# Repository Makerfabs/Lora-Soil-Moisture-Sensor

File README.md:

# Lora Soil Moisture Sensor

[toc]

# Makerfabs

[Makerfabs home page](https://www.makerfabs.com/)

[Makerfabs Wiki](https://makerfabs.com/wiki/index.php?title=Main_Page)

# Lora Soil Moisture Sensor

## Introduce

Product Link: [Lora_Soil_Moisture_Sensor](https://www.makerfabs.com/lora-soil-moisture-sensor.html)

Wiki Link:  [Lora_Soil_Moisture_Sensor_V3](https://www.makerfabs.com/wiki/index.php?title=Lora_Soil_Moisture_Sensor_V3)

The Lora soil moisture sensor is based on Atmel's Atmega328P, it collects local air temperature/ humidity with sensor AHT10, and detect the soil humidity with capacitor-humility measurement solution with MCU clock, and transmit the local environment data to the gateway, with Lora communication, suit for applications for smart-farm, irrigation, agriculture, etc. 

In applications, always you do not need to check the air/soil state continuously, have a test of them for few seconds after then minutes/hours sleeping is normally Ok for most projects. To save power, there the Air/ Soil measuring functional could be shut down in the working, so they can be only powered ON a short time and then a long time power off. With MCU in sleeping mode and low power consumption Lora module, this module works ok with 2 AAA battery more than one year. Besides, this sensor is coated with waterproof paint, which makes it longer working time in damp soil. 

## Feature

- Classic ATMEL AVR 8-bit Atmega328P, with Arduino Pro Mini(3.3V/8M bootloader pre-loaded) .
- Capacitor-humility measurement.
- AHT10 temperature and humidity sensor.
- Working with 2 AAA more than one years.
- 3D printed case.
- Waterproof coating.
- Unique ID, can be used directly without secondary programming.

# Version
## V3 
In the latest version, the 555 chip has been removed so that the sleep current can be as low as 7.1uA. And added UID, can be used directly.

**More details, see readme. md in the [V3](https://github.com/Makerfabs/Lora-Soil-Moisture-Sensor/tree/master/V3) folder.**
# Makerfabs Soil Moisture Sensor V3 For the Helium Network
Adapted from <https://hackaday.io/project/180796-lorawan-soil-moisture-sensor>

## Equipment needed:

|Sensor|<https://www.makerfabs.com/lora-soil-moisture-sensor-v3.html>||
| :- | :- | :- |
|3.3V USB to TTL / Serial converter|<https://www.makerfabs.com/cp2104-usb-to-serial-converter.html>|Makerfabs recommended|
||<https://ftdichip.com/products/ttl-232r-3v3/>|Arduino recommended|
||<https://www.sparkfun.com/products/9873>|Arduino recommended|
||[https://www.amazon.com/Serial-Adapter-Signal-Prolific-Windows/dp/B07R8BQYW1/](https://www.amazon.com/Serial-Adapter-Signal-Prolific-Windows/dp/B07R8BQYW1/ref=rvi_sccl_3/130-8941171-3218759?pd_rd_w=pLTyv&content-id=amzn1.sym.f5690a4d-f2bb-45d9-9d1b-736fee412437&pf_rd_p=f5690a4d-f2bb-45d9-9d1b-736fee412437&pf_rd_r=2VXNT4N0YP2KE4HXH7XZ&pd_rd_wg=rzSKu&pd_rd_r=5e7c75ef-e88f-4056-a7fc-fb7d07ab074c&pd_rd_i=B07R8BQYW1&psc=1)|Not ideal, but what I had lying around|
||[https://www.amazon.com/dp/B07X4ZTRD2](https://www.amazon.com/dp/B07X4ZTRD2?psc=1&ref=ppx_yo2ov_dt_b_product_details)|did NOT work|
|Dupont wire and header pins||optional depending on converter|

## Connecting and uploading to the board:

1. Use EITHER the power output of the USB-TTL converter OR batteries to power the sensor, not both
2. If the USB-TTL converter does not have DTR, you must use the RST button on the sensor to upload a sketch: hold down RST, press upload, wait until the status shows "uploading", immediately release RST
3. If connection does not work, try reversing RX and TX
4. What worked for me: sensor powered by batteries; converter GND, RX, TX only connected, RX-TX reversed

## Software needed:
* MCCI LoRaWAN LMIC library <https://github.com/mcci-catena/arduino-lmic>
* Lightweight low power library for Arduino <https://github.com/rocketscream/Low-Power>
* For original source code and additional information, refer to: <https://hackaday.io/project/180796-lorawan-soil-moisture-sensor>

## Helium setup:
1. Pay careful attention to the byte order and order of the variables APPEUI, DEVEUI, APPKEY. These are different than what is displayed in the helium console by default
2. The decoder here is provided for reference, it has not been modified to work on the helium console

## Reference info:

* ATMEL AVR 8-bit Atmega328P, with Arduino Pro Mini(3.3V/8M bootloader pre-loaded)
* AHT10 temperature and humidity sensor
* <https://docs.arduino.cc/retired/getting-started-guides/ArduinoProMini>

## V2
Old version, containing 555 chip. A number of items are provided as references.

**More details, see readme. md in the [V2](https://github.com/Makerfabs/Lora-Soil-Moisture-Sensor/tree/master/V2) folder.**

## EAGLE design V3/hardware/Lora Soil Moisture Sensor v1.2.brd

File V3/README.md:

# Lora Soil Moisture Sensor V3

```c++
/*
Version:		V5.0
Author:			UNKOWN
Create Date:	UNKOWN
Note:
	2021/12/15	V5.2: Fix RadioHead demo can't setModemConfig. 
	2021/11/17  V5.1: Fix code bug,example "ESP32 Receiver" pin define wrong.
	2021/10/22	V5.0: Modify the document structure. 
	2021/9/26	V4.0: The new hardware removed the 555 chip, updated the BOM, and significantly improved battery life.
	2021/8/24	V3.1: Now can read ADC value without 555.
	2021/7/22	V3.0: Now support Lorawan to TTN.
	2020/10/26	v2.2: Add a power-save verson.Using watch dog and sleep mode.
	2020/8/24	v2.1: Add pcb file.
    2020/7/24	v2.0: Rebuid readme,add pic. By Vincent
*/
```

[toc]

# Makerfabs

[Makerfabs home page](https://www.makerfabs.com/)

[Makerfabs Wiki](https://makerfabs.com/wiki/index.php?title=Main_Page)

# Lora Soil Moisture Sensor V3

## Introduce

Product Link: [Lora_Soil_Moisture_Sensor](https://www.makerfabs.com/lora-soil-moisture-sensor.html)

Wiki Link:  [Lora_Soil_Moisture_Sensor_V3](https://www.makerfabs.com/wiki/index.php?title=Lora_Soil_Moisture_Sensor_V3)

The Lora soil moisture sensor is based on Atmel's Atmega328P, it collects local air temperature/ humidity with sensor AHT10, and detect the soil humidity with capacitor-humility measurement solution with MCU clock, and transmit the local environment data to the gateway, with Lora communication, suit for applications for smart-farm, irrigation, agriculture, etc. 

In applications, always you do not need to check the air/soil state continuously, have a test of them for few seconds after then minutes/hours sleeping is normally Ok for most projects. To save power, there the Air/ Soil measuring functional could be shut down in the working, so they can be only powered ON a short time and then a long time power off. With MCU in sleeping mode and low power consumption Lora module, this module works ok with 2 AAA battery more than one year. Besides, this sensor is coated with waterproof paint, which makes it longer working time in damp soil. 

## Feature

- Classic ATMEL AVR 8-bit Atmega328P, with Arduino Pro Mini(3.3V/8M bootloader pre-loaded) .
- Capacitor-humility measurement.
- AHT10 temperature and humidity sensor.
- Working with 2 AAA more than one years.
- 3D printed case.
- Waterproof coating.
- Unique ID, can be used directly without secondary programming.

## Hardware Update

We removed the 555 chip and made a lot of changes to the code. The current soil moisture test uses MCU clock pulses instead of those generated by the 555 chip. Sleep mode has also been optimized more.

Detailed power consumption data is being edited....

## Firmware

### Moisture_LowPower_RadioLib_v2.1.ino

The latest firmware is in:

V3\firmware\Moisture_LowPower_RadioLib_v2.1

### How to use
- The code contains a unique ID and sends Lora messages every 75 minutes in the following format:

```c++
String message = 
    "INEDX:" + (String)packetnum + " H:" + (String)humidity + 
    " T:" + (String)temperature + " ADC:" + (String)sensorValue + 
    " BAT:" + (String)batValue;

String back_str = node_id + " REPLY : SOIL " + message;

//Full message example:
//ID010123 REPLY : SOIL INEDX:0 H:48.85 T:30.50 ADC:896 BAT:1016
```

- If you want to change the time, you can change it:

```c++
//Set sleep time, when value is 1 almost sleep 20s,when value is 450, almost 1 hour.
//Each sleep cycle almost 8s.
#define SLEEP_CYCLE 1

```

- The degree of soil ADC is about 900 in air (completely dry) and 600 in water (completely wet).

## Usage

### Receiver

A simple receiver demo is provided. You can use another Lora Moisture or Maduino Lora Radio as the receiver.

Receive data through serial port display.

The receiver code is in: V3\example\Lora_Receiver_v1.0

### ESP32 Receiver

A simple receiver demo is provided. You can use a MakePython Lora as the receiver.

Receive data and display on SSD1306.

### RadioHead Demo

The default parameters of RadioLib can reach about 800m communication distance, of course can be further, but we do not have time to debug Lora parameters.

We provide an example that can reach 1.7km communication distance, which was debugged by a former colleague. It used to depend on some AVR libraries This made ESP32 unable to complier ReadHead library at the time, so we switched to RadioLib instead. But the latest version, ReadHead is available under ESP32.

Please download the latest [RadioHead](http://www.airspayce.com/mikem/arduino/RadioHead/)

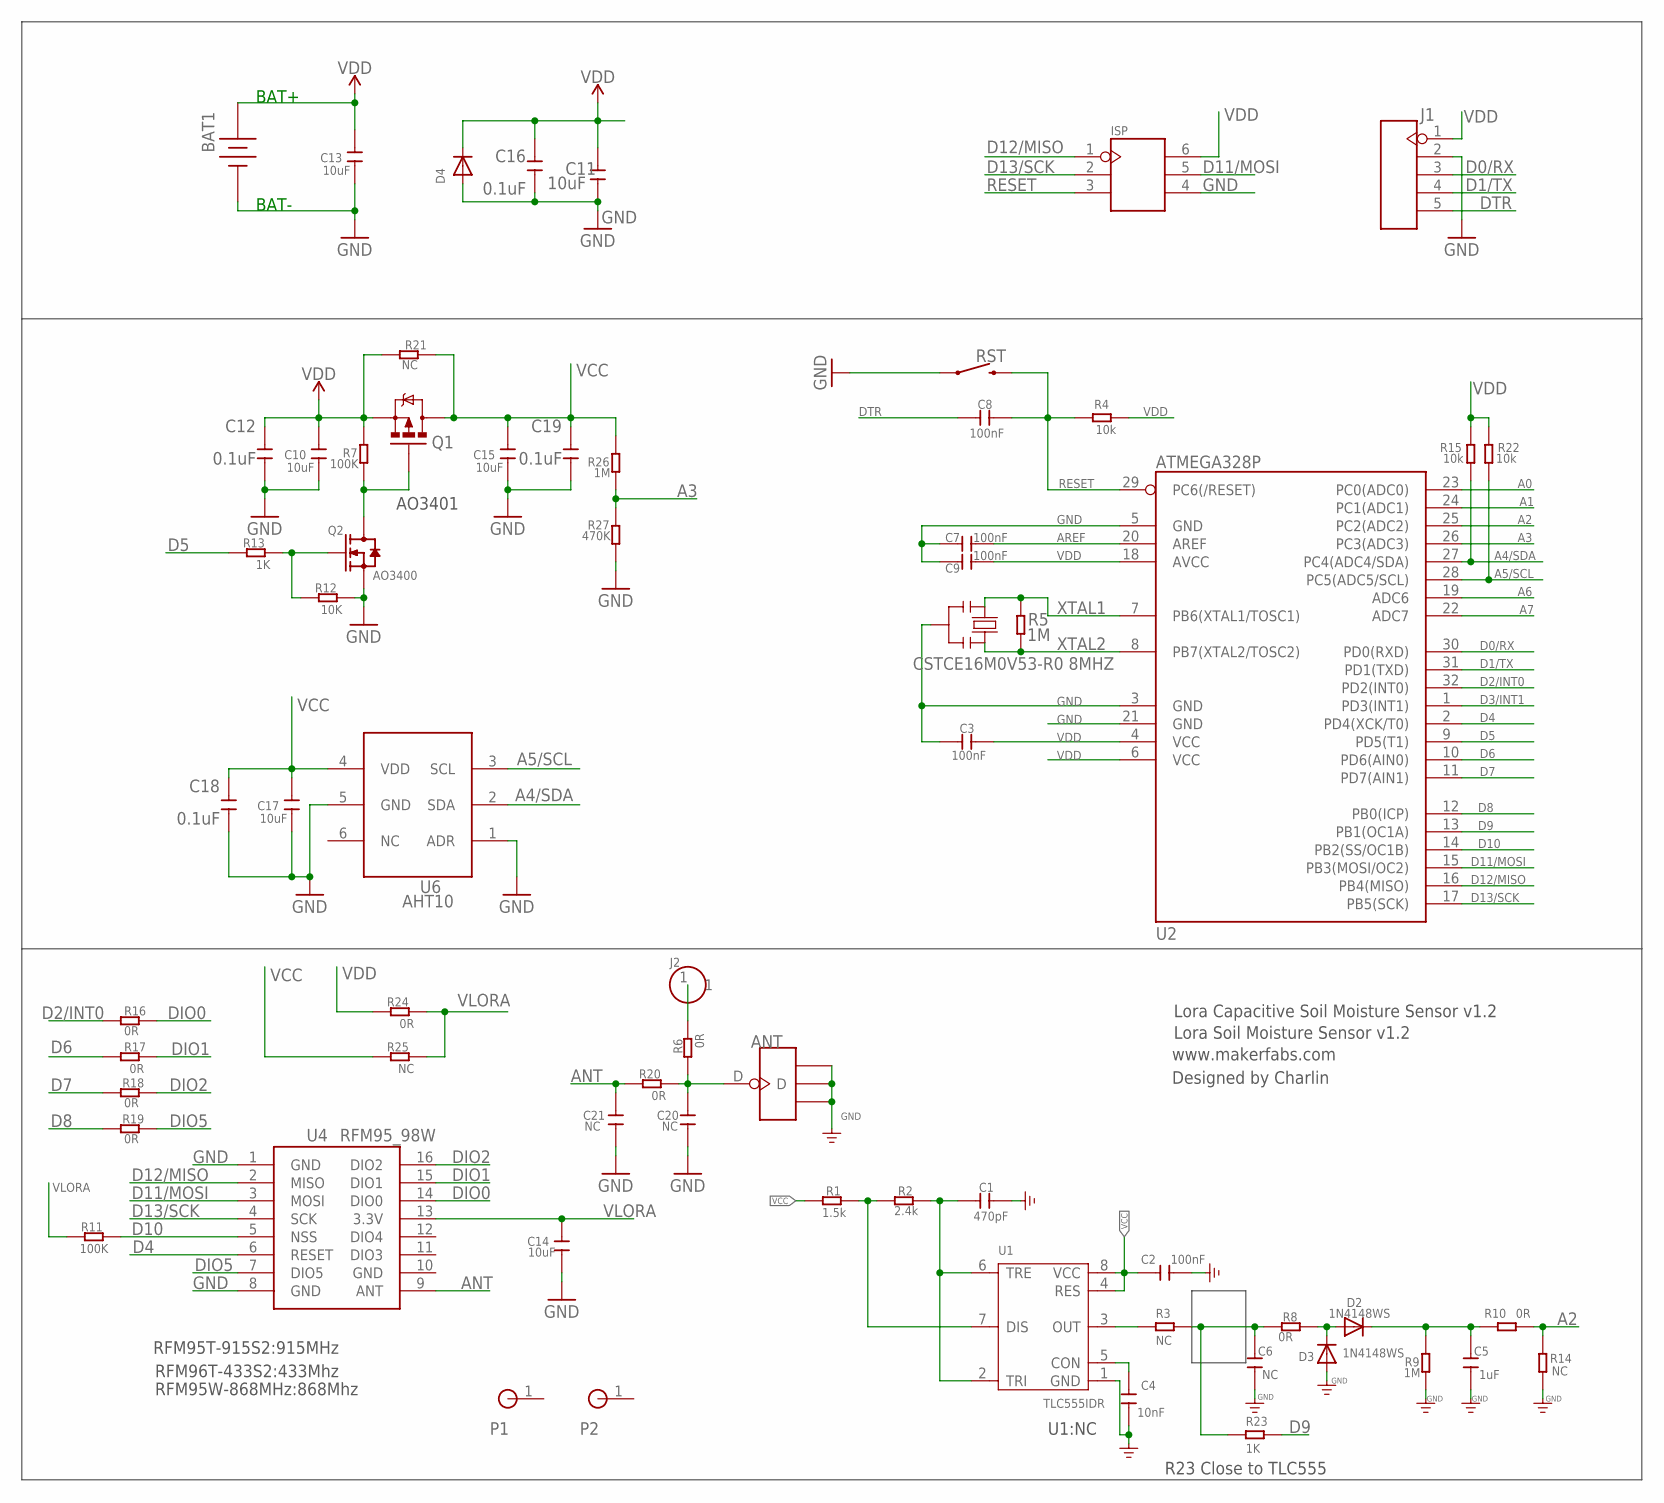
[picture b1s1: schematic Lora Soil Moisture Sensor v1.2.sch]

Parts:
ANT: ANTENNA-U-FL; 4P-U-FL
BAT1: 18650
C1: 470pF; C0603
C2: 100nF; C0603
C3, C7, C8, C9: 100nF; 0603
C4: 10nF; C0603
C5: 1uF; DISCRETE_C0603
C6: NC; DISCRETE_C0603
C10, C11, C13, C14, C15, C17: 10uF; 0603
C12, C16, C18, C19: 0.1uF; 0603
C20, C21: NC; 0603
D2, D3: 1N4148WS; SOD-323F
D4: DIODESOD-323F; SOD-323F
ISP: HEADER-2X3P-SMD; 2X3P-2.54-SMD
J1: HEADER-5P-2.54; 5P-2.54
J2: HEADER-1P-50; 1P-100/50MIL
P1, P2: HOLE-P1-2.2; MTGNP1-220-1MM
Q1: MOSFET-PCHANNEL; SOT23-3
Q2: AO3400; DISCRETE_SOT23
R1: 1.5k; R0603
R2: 2.4k; R0603
R3, R14, R21, R25: NC; R0603
R4, R15, R22: 10k; R0603
R5, R9, R26: 1M; R0603
R6, R8, R10, R16, R17, R18, R19, R20, R24: 0R; R0603
R7, R11: 100K; R0603
R12: 10K; R0603
R13, R23: 1K; R0603
R27: 470K; R0603
RST: MOMENTARY-SWITCH-SPST-SMD-6.0X3.5MM; TACTILE_SWITCH_SMD_6.0X3.5MM
U1: TLC555IDR; SOIC8-1.27-5X4MM
U2: ATMEGA328P; TQFP32
U4: RFM95_98W; RFM92_93W
U6: AHT10; SMD6-127P-400L500W
Y1: CSTCE16M0V53-R0 8MHZ; RESONATOR

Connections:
A0: U2.23 (PC0(ADC0))
A1: U2.24 (PC1(ADC1))
A2: R10.2, R14.1, U2.25 (PC2(ADC2))
A3: R26.1, R27.2, U2.26 (PC3(ADC3))
A4/SDA: R15.2, U2.27 (PC4(ADC4/SDA)), U6.2 (SDA)
A5/SCL: R22.2, U2.28 (PC5(ADC5/SCL)), U6.3 (SCL)
A6: U2.19 (ADC6)
A7: U2.22 (ADC7)
ANT: C21.2, R20.2, U4.9 (ANT)
AREF: C7.2, U2.20 (AREF)
D0/RX: J1.3, U2.30 (PD0(RXD))
D1/TX: J1.4, U2.31 (PD1(TXD))
D2/INT0: R16.1, U2.32 (PD2(INT0))
D3/INT1: U2.1 (PD3(INT1))
D4: U2.2 (PD4(XCK/T0)), U4.6 (RESET)
D5: R13.2, U2.9 (PD5(T1))
D6: R17.1, U2.10 (PD6(AIN0))
D7: R18.1, U2.11 (PD7(AIN1))
D8: R19.1, U2.12 (PB0(ICP))
D9: R23.2, U2.13 (PB1(OC1A))
D10: R11.1, U2.14 (PB2(SS/OC1B)), U4.5 (NSS)
D11/MOSI: ISP.5, U2.15 (PB3(MOSI/OC2)), U4.3 (MOSI)
D12/MISO: ISP.1, U2.16 (PB4(MISO)), U4.2 (MISO)
D13/SCK: ISP.2, U2.17 (PB5(SCK)), U4.4 (SCK)
DIO0: R16.2, U4.14 (DIO0)
DIO1: R17.2, U4.15 (DIO1)
DIO2: R18.2, U4.16 (DIO2)
DIO5: R19.2, U4.7 (DIO5)
DTR: C8.1, J1.5
GND: ANT.GND1, ANT.GND2, ANT.GND3, BAT1.2, C1.1, C2.1, C3.1, C4.2, C5.1, C6.1, C7.1, C9.1, C10.1, C11.1, C12.1, C13.1, C14.1, C15.1, C16.1, C17.1, C18.1, C19.1, C20.1, C21.1, D3.A, D4.A, ISP.4, J1.2, Q2.2 (S), R9.1, R12.1, R14.2, R27.1, RST.1, U1.1 (GND), U2.3 (GND), U2.5 (GND), U2.21 (GND), U4.1 (GND), U4.8 (GND), U4.10 (GND), U6.1 (ADR), U6.5 (GND), Y1.2
unnamed: R1.1, R2.2, U1.7 (DIS)
unnamed: C1.2, R2.1, U1.2 (TRI), U1.6 (TRE)
unnamed: C4.1, U1.5 (CON)
unnamed: R3.1, U1.3 (OUT)
unnamed: C6.2, R3.2, R8.1, R23.1
unnamed: J2.1, R6.1
unnamed: Q1.1 (G), Q2.3 (D), R7.1
unnamed: D2.A, D3.C, R8.2
unnamed: Q2.1 (G), R12.2, R13.1
unnamed: C5.2, D2.C, R9.2, R10.1
unnamed: ANT.D, C20.2, R6.2, R20.1
RESET: C8.2, ISP.3, R4.2, RST.2, U2.29 (PC6(/RESET))
VCC: C2.2, C15.2, C17.2, C18.2, C19.2, Q1.3 (D), R1.2, R21.1, R25.2, R26.2, U1.4 (RES), U1.8 (VCC), U6.4 (VDD)
VDD: BAT1.1, C3.2, C9.2, C10.2, C11.2, C12.2, C13.2, C16.2, D4.C, ISP.6, J1.1, Q1.2 (S), R4.1, R7.2, R15.1, R21.2, R22.1, R24.2, U2.4 (VCC), U2.6 (VCC), U2.18 (AVCC)
VLORA: C14.2, R11.2, R24.1, R25.1, U4.13 (3.3V)
XTAL1: R5.2, U2.7 (PB6(XTAL1/TOSC1)), Y1.1
XTAL2: R5.1, U2.8 (PB7(XTAL2/TOSC2)), Y1.3

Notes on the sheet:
RFM95T-915S2:915MHz
RFM96T-433S2:433Mhz
RFM95W-868MHz:868Mhz
Lora Soil Moisture Sensor v1.2
R23 Close to TLC555
www.makerfabs.com
Lora Capacitive Soil Moisture Sensor v1.2
Designed by Charlin
BAT+
BAT-
AO3401
U1:NC

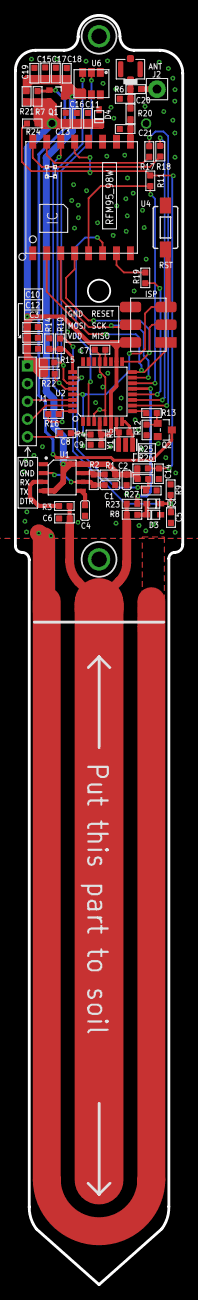
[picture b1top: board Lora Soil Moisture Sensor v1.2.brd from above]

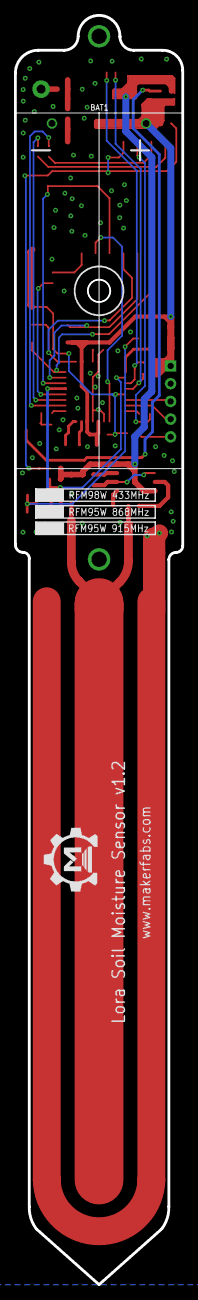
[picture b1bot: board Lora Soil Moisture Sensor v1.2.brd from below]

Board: 2 copper layers, 24.0 x 182.0 mm, 67 parts (2 on the bottom side), 42 nets.

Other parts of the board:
U$7: MAKERFABS_0.3

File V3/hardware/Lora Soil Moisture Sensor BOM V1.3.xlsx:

Lora Capacitive Soil Moisture Sensor v1.3
Part | Value | Device | Package | Description | Qty
双面胶 |  |  |  |  | 1 | 双面胶将电池座黏到PCB上之后焊接
BAT1 | 2节AAA电池座，带针 |  |  |  | 1
ANT | 天线座 | ANTENNA-U-FL | 4P-U-FL |  | 1
C10,C11,C13,C14 | 10uF | C-0603 | 0603 | Ceramic Capacitors | 4
C1 | 470pF,0603 | C-0603 | 0603 |  | 1
C2,C3,C7,C8,C9,C12,C16,C18,C19 | 100nF | C-0603 | 0603 |  | 9
C4 | 10nF | C-0603 | 0603 |  | 1
C5 | 1uF | C-0603 | 0603 |  | 1
D2,D3,D4 | 1N4148WS | SOD-323 | SOD-323 |  | 3
R5,R9,R26 | 1M/1% | R-0603 | R0603 |  | 4
R27 | 470K/1% | R-0603 | R0603 |  | 1
R4,R12,R15,R22, | 10K | R-0603 | R0603 |  | 5
R13,R23 | 1K | R-0603 | R0603 |  | 2
R2 | 2.4K | R-0603 | R0603 |  | 1
R1 | 1.5k | R-0603 | R0603 |  | 1
R11,R7 | 100K/1% | R-0603 | R0603 |  | 2
R6,R8,R10,R16,R17,R18,R19,R20,R24 | 0R | R-0603 | R0603 |  | 9
U2 | ATMEGA328P | TQFP32 | TQFP32 | MICROCONTROLLER | 1
U4 | Lora模块，433M/868M/915M |  |  |  | 1 | 订单不同，模块不同，配相应频段的天线
U6 | AHT10 |  |  |  | 1
Q2 | AO3400 | SOT23 |  |  | 1
Q1 | AO3401 | SOT23 |  |  | 1
Y1 | CSTCE8M00,8MHZ,3P | SMD3213 | RESONATOR |  | 1
RST | 贴片按键，2P,6.0*3.5 |  |  |  | 1
小标签贴纸 | 背粘胶亚银标签，20mm*6mm,圆角，范围ID010000至ID019999 |  |  | 贴在PCBA上 | 1
大标签贴纸 | 背粘胶亚银标签，30mm*10mm,圆角,范围ID010000至ID019999 |  |  | 贴在外壳上 | 1
三防漆-国产J3166型号的漆 | 要求对板子进行喷三防油漆处理 |  |  | J3166型号漆
868Mhz/915MHz弹簧天线 |  |  |  |  | 1
433Mhz弹簧天线 |  |  |  |  | 1

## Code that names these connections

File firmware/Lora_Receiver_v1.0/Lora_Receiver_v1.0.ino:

/*
   LoRaLib Receive Example

   This example listens for LoRa transmissions and tries to
   receive them. To successfully receive data, the following
   settings have to be the same on both transmitter
   and receiver:
    - carrier frequency
    - bandwidth
    - spreading factor
    - coding rate
    - sync word
    - preamble length

   For more detailed information, see the LoRaLib Wiki
   https://github.com/jgromes/LoRaLib/wiki

   For full API reference, see the GitHub Pages
   https://jgromes.github.io/LoRaLib/
*/

// include the library
#include <RadioLib.h>
#include <SPI.h>
#include "avr/boot.h"

// create instance of LoRa class using SX1278 module
// this pinout corresponds to RadioShield
// https://github.com/jgromes/RadioShield

#define DIO0 2
#define DIO1 6
//#define DIO2 7
//#define DIO5 8

#define LORA_RST 9
#define LORA_CS 10

#define SPI_MOSI 11
#define SPI_MISO 12
#define SPI_SCK 13


/*
Begin method:
Carrier frequency: 434.0 MHz (for SX1276/77/78/79 and RFM96/98) or 915.0 MHz (for SX1272/73 and RFM95/97)
Bandwidth: 125.0 kHz (dual-sideband)
Spreading factor: 9
Coding rate: 4/7
Sync word: SX127X_SYNC_WORD (0x12)
Output power: 10 dBm
Preamble length: 8 symbols
Gain: 0 (automatic gain control enabled)
Other:
Over-current protection: 60 mA
Inaccessible:
LoRa header mode: explicit
Frequency hopping: disabled

*/

#define FREQUENCY 434.0
#define BANDWIDTH 125.0
#define SPREADING_FACTOR 9
#define CODING_RATE 7
#define OUTPUT_POWER 10
#define PREAMBLE_LEN 8
#define GAIN 0

SX1278 radio = new Module(LORA_CS, DIO0, LORA_RST, DIO1);
//SX1278 radio = new Module(LORA_CS, DIO0, LORA_RST, DIO1, SPI, SPISettings());


void setup() {
  Serial.begin(115200);

  // initialize SX1278 with default settings
  Serial.print(F("Initializing ... "));

  //int state = radio.begin();
  int state = radio.begin(FREQUENCY, BANDWIDTH, SPREADING_FACTOR, CODING_RATE, SX127X_SYNC_WORD, OUTPUT_POWER, PREAMBLE_LEN, GAIN);
  if (state == ERR_NONE) {
    Serial.println(F("success!"));
  } else {
    Serial.print(F("failed, code "));
    Serial.println(state);
    while (true);
  }
  Serial.print(F("Waiting for incoming transmission ... "));
}

void loop() {
  //Serial.print(F("Waiting for incoming transmission ... "));

  // you can receive data as an Arduino String
  // NOTE: receive() is a blocking method!
  //       See example ReceiveInterrupt for details
  //       on non-blocking reception method.
  // NOTE: for spreading factor 6, the packet length
  //       must be known in advance, and provided to
  //       receive() method!
  String str;
  int state = radio.receive(str);

  // you can also receive data as byte array
  /*
    size_t len = 8;
    byte byteArr[len];
    int state = radio.receive(byteArr, len);
  */

  if (state == ERR_NONE) {
    // packet was successfully received
    Serial.println(F("success!"));

    // print data of the packet
    Serial.print(F("Data:\t\t\t"));
    Serial.println(str);

    // print RSSI (Received Signal Strength Indicator)
    // of the last received packet
    Serial.print(F("RSSI:\t\t\t"));
    Serial.print(radio.getRSSI());
    Serial.println(F(" dBm"));

    // print SNR (Signal-to-Noise Ratio)
    // of the last received packet
    Serial.print(F("SNR:\t\t\t"));
    Serial.print(radio.getSNR());
    Serial.println(F(" dB"));

    // print frequency error
    // of the last received packet
    Serial.print(F("Frequency error:\t"));
    Serial.print(radio.getFrequencyError());
    Serial.println(F(" Hz"));

  } else if (state == ERR_RX_TIMEOUT) {
    // timeout occurred while waiting for a packet
    //Serial.println(F("timeout!"));

  } else if (state == ERR_CRC_MISMATCH) {
    // packet was received, but is malformed
    Serial.println(F("CRC error!"));

  }

}

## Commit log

2020-07-24 rebuid readme
2020-08-24 add pcb
2020-10-26 v2.2 power save
2021-07-22 Support Lorawan
2021-08-24 Add no555
2021-09-16 Add new firmware
2021-09-17 Repair battery read adc bug.
2021-09-26 V4.0
2021-10-06 Change file position
2021-10-22 Reorganize the file structure
2021-10-22 Edit Readme
2021-10-22 create MakePython ESP32 receiver
2021-10-26 Add radiohead demo
2021-11-17 Change Pin Define
2021-12-15 V5.2
2022-09-01 Update README.md
    Added V3 Helium info
2022-09-01 Added the code for the Helium Network
2025-10-24 Add demo
2025-11-03 Remove errant semicolon which caused json delimiter to be clipped/truncated between Bat and Humitidty values
    Truncated delimiter produces:
    ...,"Bat":910"Humidity":74.07,...
    Expected json string:
    ...,"Bat":910,"Humidity":74.07,...

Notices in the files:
parts and their libraries:
User-Submitted: Licensing: Creative Commons ShareAlike 4.0 International - https://creativecommons.org/licenses/by-sa/4.0
